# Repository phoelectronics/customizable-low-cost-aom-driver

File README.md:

# customizable-low-cost-aom-driver
Designed by Parker Osborne, University of San Diego
A custom low-cost four-channel RF signal generator that costs about $250 per board. Built around an Analog Devices AD9959 direct digital synthesizer, clocked and controlled by a raspberry Pi Pico 2W (RP2350). Features per channel: 9th order Nyquist image suppression filter, resistive pads for match and flatness, monolithic amplifier stage, +10 dBm delivered at SMA output. Tuned for 50-150 MHz output band.

The low-cost gen is built on a 4-layer RF PCB, fabricated by OSHPark. Note: When the PCB was order for the current version, a supply shortage led to a non-standard insulating core being used in this design, compared to the usual service. A stencil used for soldering the AD9959 and surround decoupling capacitors was ordered from OSH Stencils. Everything was assembled by hand using a soldering iron, hotplate, and digital microscope.

Current Version and Notes:
The low-cost generator is currently in its first working version. A second version is currently planned, with noted changes below. This design is open source and intended to be used for atomic, molecular, and optics physics, but can be implemented in a wide variety of fields. We are currently using it for doppler cooling Rb-87 atoms to create Bose-Einstein condensates. 

Current software control is limited to basic testing functions, routines can be written and triggered using spare Pico GPIO pins but are not provided here.

A full proceedings paper write up is currently planned and will be added here when completed. Currently in the final testing phase of the first design.

Note: A power supply failure burnt out the synthesizer while testing in the current version. It is suggested to remove the Vsys Pin (39) from the Raspberry Pi Pico if communication over USB serial is to be used. 

Changes for Version 2:
- adding power supply protection
- adding current limiting resistor of chip select line 
- shrinking package size of capacitors in filter

  Please reach out to me if you have any questions.

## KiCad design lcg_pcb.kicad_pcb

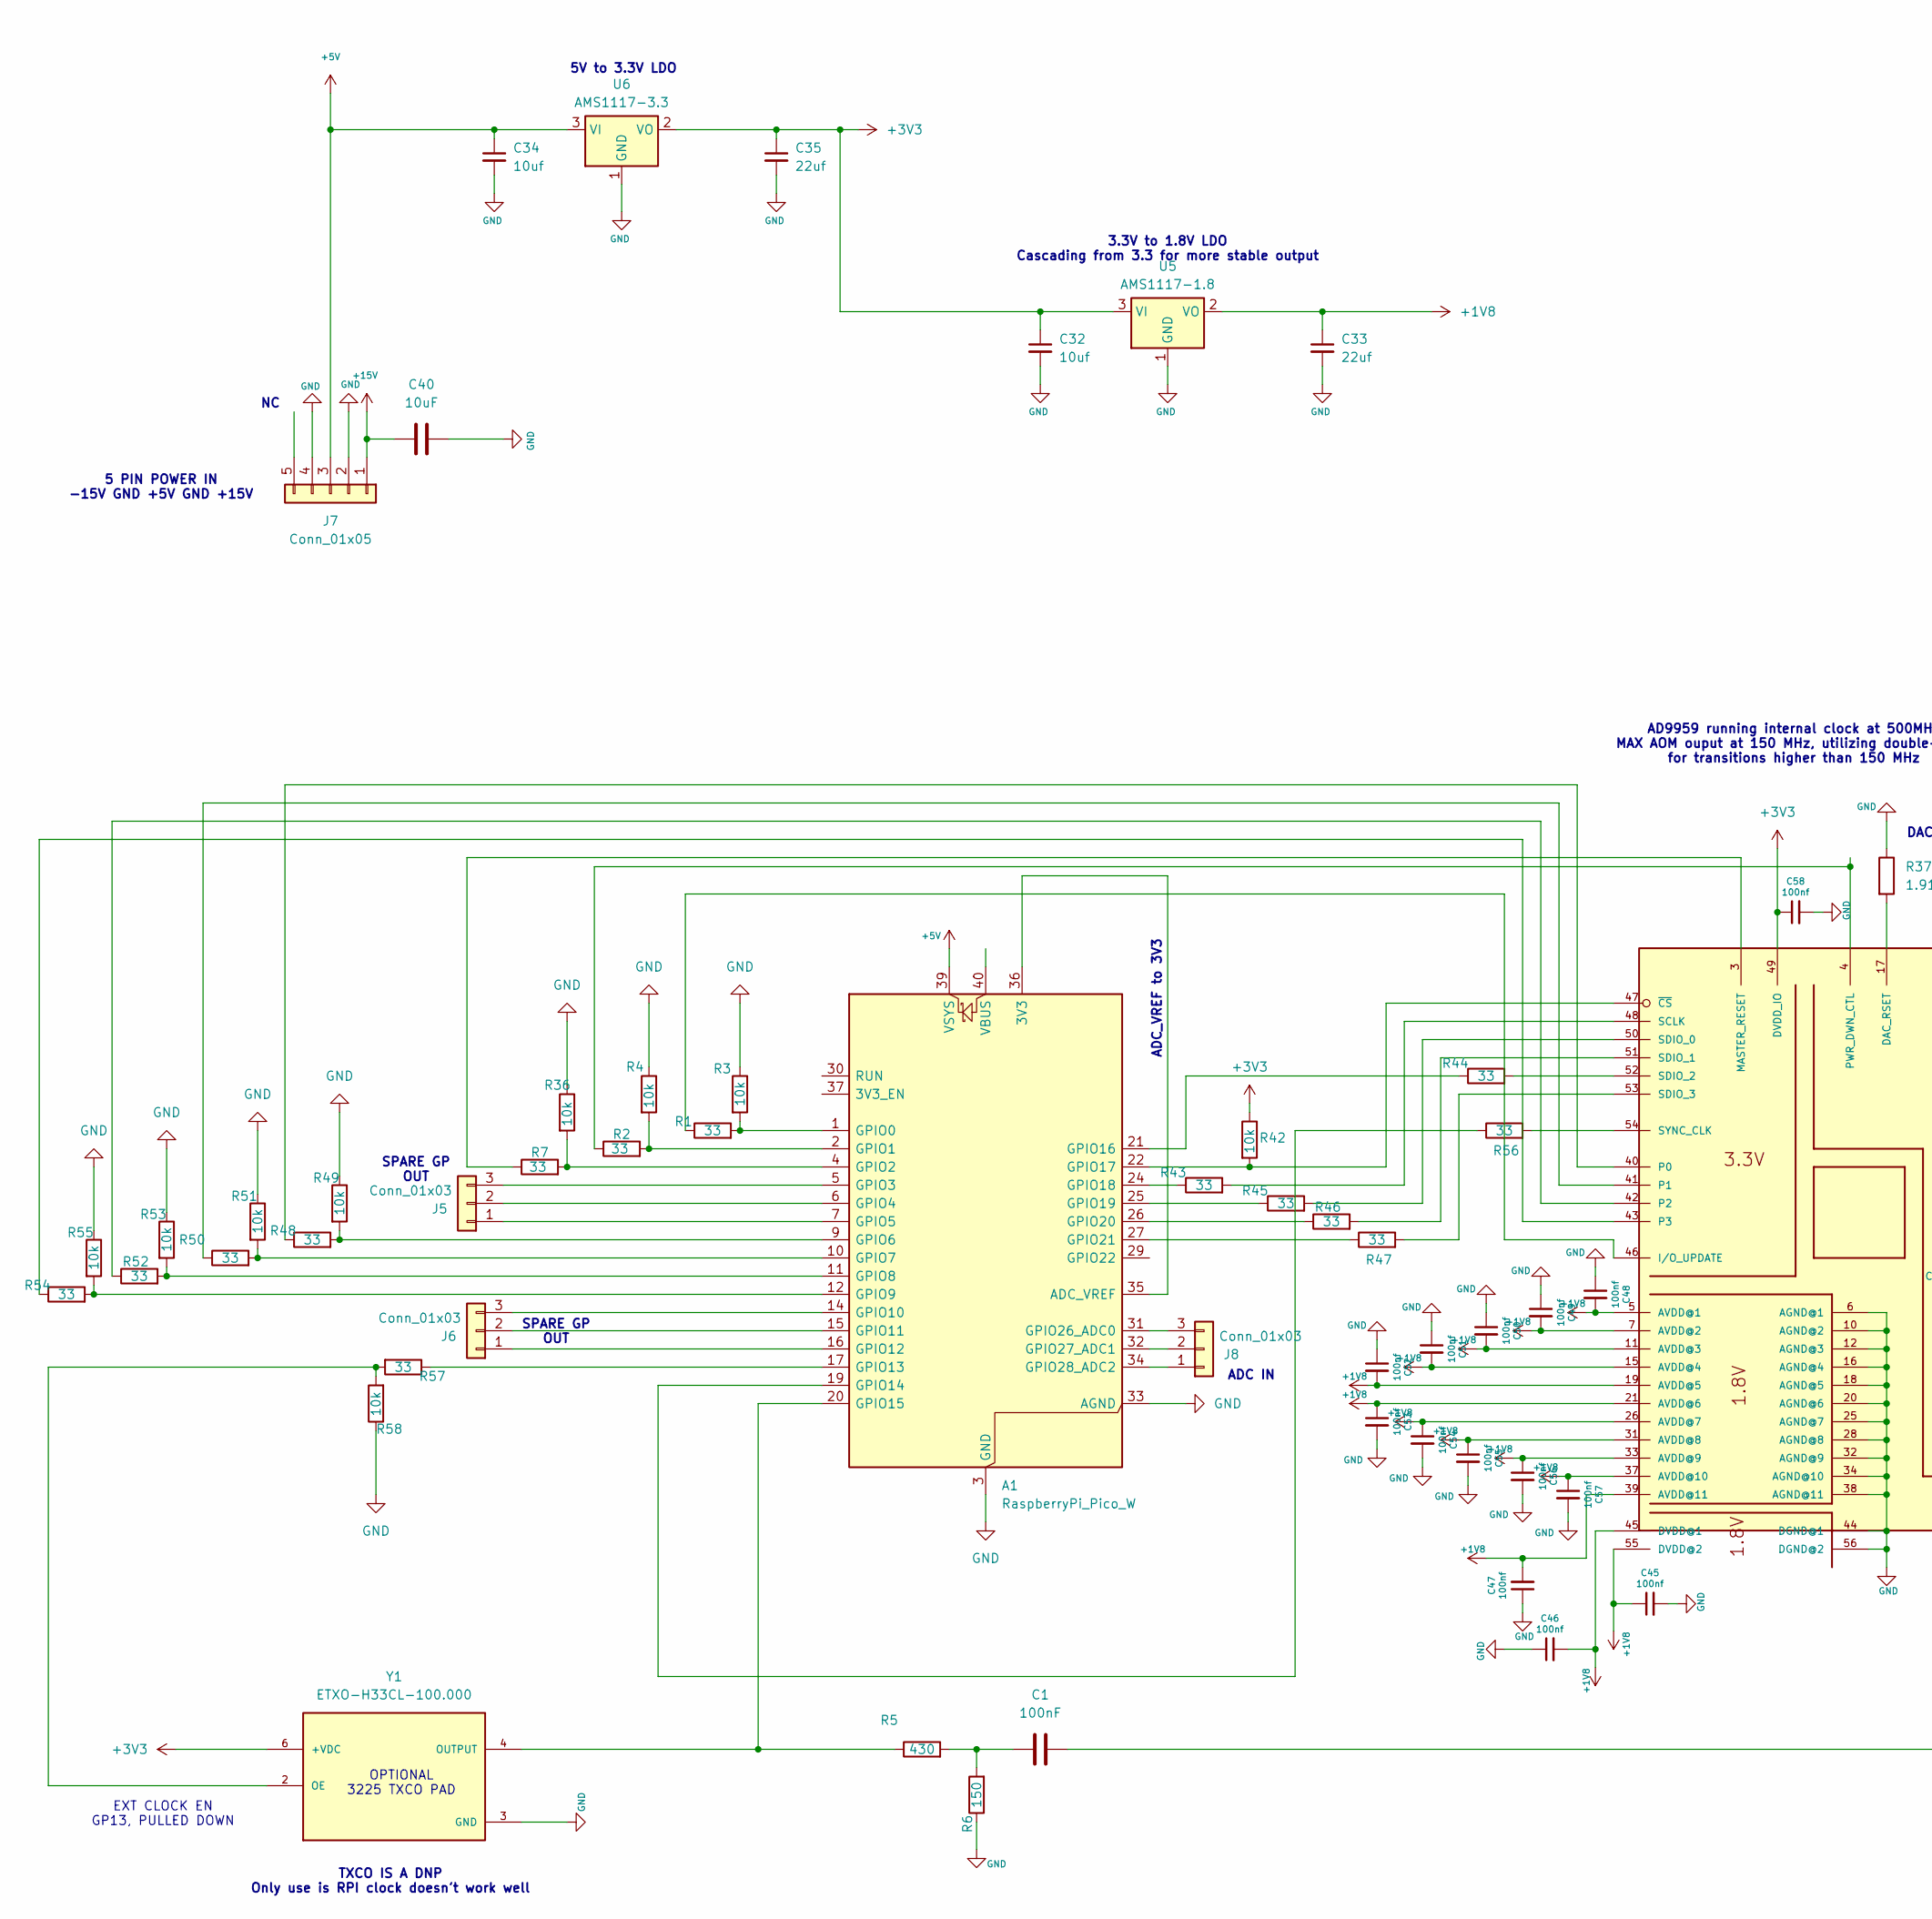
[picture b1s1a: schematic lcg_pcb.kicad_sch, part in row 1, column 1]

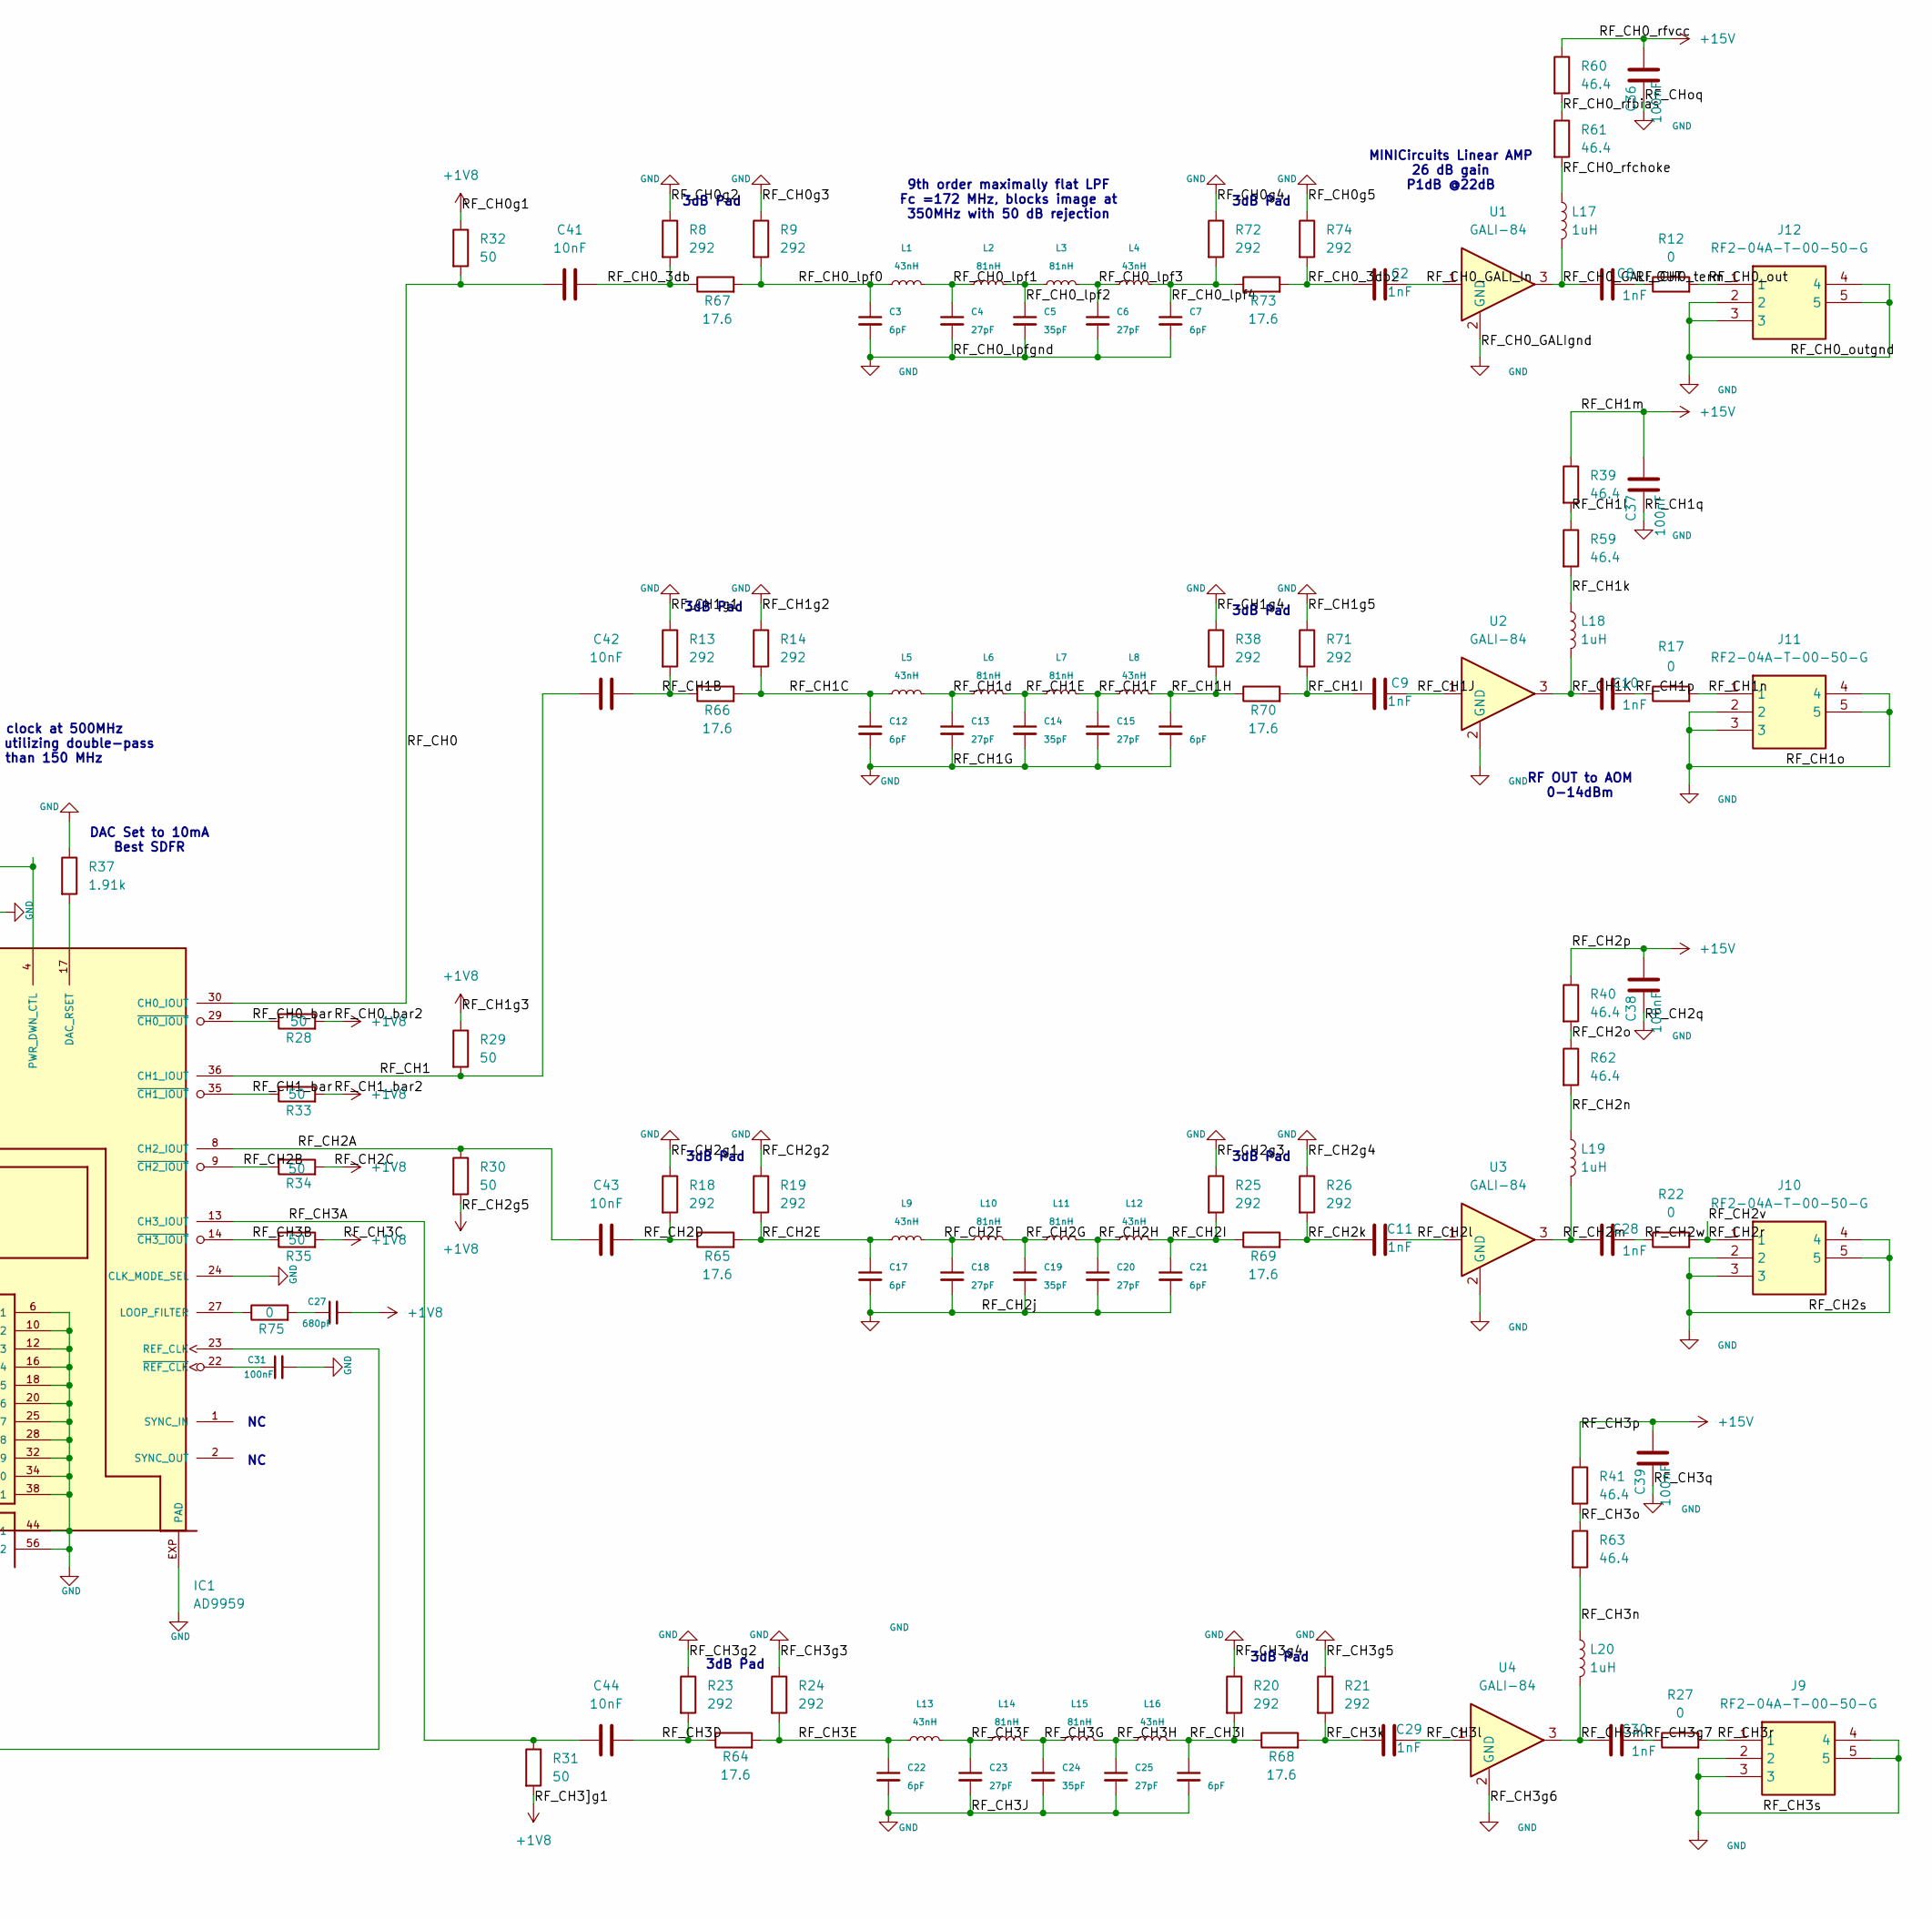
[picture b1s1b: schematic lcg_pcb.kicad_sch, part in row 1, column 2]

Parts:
A1: RaspberryPi_Pico_W; RaspberryPi_Pico_Common_THT
C1, C31, C36, C37, C38, C39: 100nF; C_1206_3216Metric_Pad1.33x1.80mm_HandSolder
C2, C8, C9, C10, C11, C28, C29, C30: 1nF; C_1206_3216Metric_Pad1.33x1.80mm_HandSolder
C3, C7, C12, C16, C17, C21, C22, C26: 6pF; C_1206_3216Metric_Pad1.33x1.80mm_HandSolder
C4, C6, C13, C15, C18, C20, C23, C25: 27pF; C_1206_3216Metric_Pad1.33x1.80mm_HandSolder
C5, C14, C19, C24: 35pF; C_1206_3216Metric_Pad1.33x1.80mm_HandSolder
C27: 680pF; C_1206_3216Metric_Pad1.33x1.80mm_HandSolder
C32, C34: 10uf; C_1206_3216Metric_Pad1.33x1.80mm_HandSolder
C33, C35: 22uf; C_1206_3216Metric_Pad1.33x1.80mm_HandSolder
C40: 10uF; C_1206_3216Metric_Pad1.33x1.80mm_HandSolder
C41, C42, C43, C44: 10nF; C_1206_3216Metric_Pad1.33x1.80mm_HandSolder
C45, C46, C47, C48, C49, C50, C51, C52, C53, C54, C55, C56, C57, C58: 100nf; C_0402_1005Metric_Pad0.74x0.62mm_HandSolder
IC1: AD9959; LFCSP56
J5, J6, J8: Conn_01x03; Molex_KK-254_AE-6410-03A_1x03_P2.54mm_Vertical
J7: Conn_01x05; Molex_KK-254_AE-6410-05A_1x05_P2.54mm_Vertical
J9, J10, J11, J12: RF2-04A-T-00-50-G; RF204AT0050G; Mouser Part Number 737-RF204AT0050G
L1, L4, L5, L8, L9, L12, L13, L16: 43nH; L_1008_2520Metric_Pad1.43x2.20mm_HandSolder
L2, L3, L6, L7, L10, L11, L14, L15: 81nH; L_1008_2520Metric_Pad1.43x2.20mm_HandSolder
L17, L18, L19, L20: 1uH; L_1206_3216Metric_Pad1.22x1.90mm_HandSolder
R1, R2, R7, R43, R44, R45, R46, R47, R48, R50, R52, R54, R56, R57: 33; R_1206_3216Metric_Pad1.30x1.75mm_HandSolder
R3, R4, R36, R42, R49, R51, R53, R55, R58: 10k; R_1206_3216Metric_Pad1.30x1.75mm_HandSolder
R5: 430; R_1206_3216Metric_Pad1.30x1.75mm_HandSolder
R6: 150; R_1206_3216Metric_Pad1.30x1.75mm_HandSolder
R8, R9, R13, R14, R18, R19, R20, R21, R23, R24, R25, R26, R38, R71, R72, R74: 292; R_1206_3216Metric_Pad1.30x1.75mm_HandSolder
R12, R17, R22, R27: 0; R_2512_6332Metric_Pad1.40x3.35mm_HandSolder
R28, R29, R30, R31, R32, R33, R34, R35: 50; R_1206_3216Metric_Pad1.30x1.75mm_HandSolder
R37: 1.91k; R_1206_3216Metric_Pad1.30x1.75mm_HandSolder
R39, R40, R41, R59, R60, R61, R62, R63: 46.4; R_2512_6332Metric_Pad1.40x3.35mm_HandSolder
R64, R65, R66, R67, R68, R69, R70, R73: 17.6; R_1206_3216Metric_Pad1.30x1.75mm_HandSolder
R75: 0; R_1206_3216Metric_Pad1.30x1.75mm_HandSolder
U1, U2, U3, U4: GALI-84; SOT-89-3
U5: AMS1117-1.8; SOT-223-3_TabPin2
U6: AMS1117-3.3; SOT-223-3_TabPin2
Y1: ETXO-H33CL-100.000; OSC_ETXO-H33CL-100.000

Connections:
+1V8: C27.2, C33.1, C45.1, C46.2, C47.2, C48.2, C49.2, C50.2, C51.2, C52.2, C53.1, C54.1, C55.1, C56.1, C57.1, IC1.5 (AVDD@1), IC1.7 (AVDD@2), IC1.11 (AVDD@3), IC1.15 (AVDD@4), IC1.19 (AVDD@5), IC1.21 (AVDD@6), IC1.26 (AVDD@7), IC1.31 (AVDD@8), IC1.33 (AVDD@9), IC1.37 (AVDD@10), IC1.39 (AVDD@11), IC1.45 (DVDD@1), IC1.55 (DVDD@2), R28.2, R29.1, R30.2, R31.2, R32.1, R33.2, R34.2, R35.2, U5.2 (VO)
+3V3: C32.1, C35.1, C58.1, IC1.49 (DVDD_IO), R42.1, U5.3 (VI), U6.2 (VO), Y1.6 (+VDC)
+5V: A1.39 (VSYS), C34.1, J7.3, U6.3 (VI)
+15V: C36.2, C37.2, C38.2, C39.2, C40.2, J7.1, R39.1, R40.1, R41.1, R60.1; also elsewhere on the board
/RF_CH0: C41.1, IC1.30 (CH0_IOUT), R32.2
/RF_CH0_3db: C41.2, R8.2, R67.1; also elsewhere on the board
/RF_CH0_3db2: C2.1, R73.2, R74.2
/RF_CH0_GALI_In: C2.2, U1.1
/RF_CH0_GALI_OUT: C8.1, L17.2, U1.3
/RF_CH0_bar: IC1.29 (~CH0_IOUT), R28.1
/RF_CH0_lpf0: C3.1, L1.1, R9.2, R67.2
/RF_CH0_lpf1: C4.1, L1.2, L2.1
/RF_CH0_lpf2: C5.1, L2.2, L3.1
/RF_CH0_lpf3: C6.1, L3.2, L4.1
/RF_CH0_lpf4: C7.1, L4.2, R72.2, R73.1
/RF_CH0_out: J12.1, R12.2
/RF_CH0_rfbias: R60.2, R61.1
/RF_CH0_rfchoke: L17.1, R61.2
/RF_CH0_term: C8.2, R12.1
/RF_CH1: C42.1, IC1.36 (CH1_IOUT), R29.2
/RF_CH1B: C42.2, R13.2, R66.1
/RF_CH1C: C12.1, L5.1, R14.2, R66.2
/RF_CH1E: C14.1, L6.2, L7.1
/RF_CH1F: C15.1, L7.2, L8.1
/RF_CH1H: C16.1, L8.2, R38.2, R70.1
/RF_CH1I: C9.1, R70.2, R71.2
/RF_CH1J: C9.2, U2.1
/RF_CH1K: C10.1, L18.2, U2.3
/RF_CH1_bar: IC1.35 (~CH1_IOUT), R33.1
/RF_CH1d: C13.1, L5.2, L6.1
/RF_CH1k: L18.1, R59.2
/RF_CH1l: R39.2, R59.1
/RF_CH1n: J11.1, R17.2
/RF_CH1p: C10.2, R17.1
/RF_CH2A: C43.1, IC1.8 (CH2_IOUT), R30.1
/RF_CH2B: IC1.9 (~CH2_IOUT), R34.1
/RF_CH2D: C43.2, R18.2, R65.1
/RF_CH2E: C17.1, L9.1, R19.2, R65.2
/RF_CH2F: C18.1, L9.2, L10.1
/RF_CH2G: C19.1, L10.2, L11.1
/RF_CH2H: C20.1, L11.2, L12.1
/RF_CH2I: C21.1, L12.2, R25.2, R69.1
/RF_CH2k: C11.1, R26.2, R69.2
/RF_CH2l: C11.2, U3.1
/RF_CH2m: C28.1, L19.2, U3.3
/RF_CH2n: L19.1, R62.2
/RF_CH2o: R40.2, R62.1
/RF_CH2r: J10.1, R22.2
/RF_CH2w: C28.2, R22.1
/RF_CH3A: C44.1, IC1.13 (CH3_IOUT), R31.1
/RF_CH3B: IC1.14 (~CH3_IOUT), R35.1
/RF_CH3D: C44.2, R23.2, R64.1
/RF_CH3E: C22.1, L13.1, R24.2, R64.2
/RF_CH3F: C23.1, L13.2, L14.1
/RF_CH3G: C24.1, L14.2, L15.1
/RF_CH3H: C25.1, L15.2, L16.1
/RF_CH3I: C26.1, L16.2, R20.2, R68.1
/RF_CH3g7: C30.2, R27.1
/RF_CH3k: C29.1, R21.2, R68.2
/RF_CH3l: C29.2, U4.1
/RF_CH3m: C30.1, L20.2, U4.3
/RF_CH3n: L20.1, R63.2
/RF_CH3o: R41.2, R63.1
/RF_CH3r: J9.1, R27.2
GND: A1.3 (GND), A1.8 (GND), A1.13 (GND), A1.18 (GND), A1.23 (GND), A1.28 (GND), A1.33 (AGND), A1.38 (GND), C3.2, C4.2, C5.2, C6.2, C7.2, C12.2, C13.2, C14.2, C15.2, C16.2, C17.2, C18.2, C19.2, C20.2, C21.2, C22.2, C23.2, C24.2, C25.2, C26.2, C31.2, C32.2, C33.2, C34.2, C35.2, C36.1, C37.1, C38.1, C39.1, C40.1, C45.2, C46.1, C47.1, C48.1, C49.1, C50.1, C51.1, C52.1, C53.2, C54.2, C55.2, C56.2, C57.2, C58.2, IC1.6 (AGND@1), IC1.10 (AGND@2), IC1.12 (AGND@3), IC1.16 (AGND@4), IC1.18 (AGND@5), IC1.20 (AGND@6), IC1.24 (CLK_MODE_SEL), IC1.25 (AGND@7), IC1.28 (AGND@8), IC1.32 (AGND@9), IC1.34 (AGND@10), IC1.38 (AGND@11), IC1.44 (DGND@1), IC1.56 (DGND@2), IC1.EXP (PAD), J7.2, J7.4, J9.2, J9.3, J9.4, J9.5, J10.2, J10.3, J10.4, J10.5, J11.2, J11.3, J11.4, J11.5, J12.2, J12.3, J12.4, J12.5, R3.1, R4.1, R6.1, R8.1, R9.1, R13.1, R14.1, R18.1, R19.1, R20.1, R21.1, R23.1, R24.1, R25.1, R26.1, R36.1, R37.1, R38.1, R49.1, R51.1, R53.1, R55.1, R58.1, R71.1, R72.1, R74.1, U1.2 (GND_2), U2.2 (GND_2), U3.2 (GND_2), U4.2 (GND_2), U5.1 (GND), U6.1 (GND), Y1.3 (GND); also elsewhere on the board
unnamed: A1.35 (ADC_VREF), A1.36 (3V3)
unnamed: A1.1 (GPIO0), R1.2, R3.2
unnamed: A1.2 (GPIO1), R2.2, R4.2
unnamed: A1.4 (GPIO2), R7.2, R36.2
unnamed: A1.5 (GPIO3), J5.3
unnamed: A1.6 (GPIO4), J5.2
unnamed: A1.7 (GPIO5), J5.1
unnamed: A1.9 (GPIO6), R48.2, R49.2
unnamed: A1.10 (GPIO7), R50.2, R51.2
unnamed: A1.11 (GPIO8), R52.2, R53.2
unnamed: A1.12 (GPIO9), R54.2, R55.2
unnamed: A1.14 (GPIO10), J6.3
unnamed: A1.15 (GPIO11), J6.2
unnamed: A1.16 (GPIO12), J6.1
unnamed: A1.17 (GPIO13), R57.1
unnamed: A1.19 (GPIO14), R56.1
unnamed: A1.20 (GPIO15), R5.1, Y1.4 (OUTPUT)
unnamed: A1.21 (GPIO16), R44.1
unnamed: A1.22 (GPIO17), IC1.47 (~CS), R42.2
unnamed: A1.24 (GPIO18), R43.1
unnamed: A1.25 (GPIO19), R45.1
unnamed: A1.26 (GPIO20), R46.1
unnamed: A1.27 (GPIO21), R47.1
unnamed: A1.31 (GPIO26_ADC0), J8.3
unnamed: A1.32 (GPIO27_ADC1), J8.2
unnamed: A1.34 (GPIO28_ADC2), J8.1
unnamed: C1.1, R5.2, R6.2
unnamed: C27.1, R75.2
unnamed: IC1.17 (DAC_RSET), R37.2
unnamed: IC1.46 (I/O_UPDATE), R1.1
unnamed: IC1.27 (LOOP_FILTER), R75.1
unnamed: IC1.3 (MASTER_RESET), R7.1
unnamed: IC1.40 (P0), R48.1
unnamed: IC1.41 (P1), R50.1
unnamed: IC1.42 (P2), R52.1
unnamed: IC1.43 (P3), R54.1
unnamed: IC1.4 (PWR_DWN_CTL), R2.1
unnamed 102: C1.2, IC1.23 (REF_CLK); also elsewhere on the board
unnamed: IC1.48 (SCLK), R43.2
unnamed 104: IC1.50 (SDIO_0), R45.2; also elsewhere on the board
unnamed: IC1.51 (SDIO_1), R46.2
unnamed: IC1.52 (SDIO_2), R44.2
unnamed: IC1.53 (SDIO_3), R47.2
unnamed: IC1.54 (SYNC_CLK), R56.2
unnamed: C31.1, IC1.22 (~REF_CLK)
unnamed: R57.2, R58.2, Y1.2 (OE)

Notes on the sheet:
ADC IN
DAC Set to 10mA Best SDFR
3dB Pad
ADC_VREF to 3V3
MINICircuits Linear AMP 26 dB gain P1dB @22dB
9th order maximally flat LPF Fc =172 MHz, blocks image at 350MHz with 50 dB rejection
SPARE GP OUT
3.3V to 1.8V LDO Cascading from 3.3 for more stable output
OPTIONAL 3225 TXCO PAD
AD9959 running internal clock at 500MHz MAX AOM ouput at 150 MHz, utilizing double-pass for transitions higher than 150 MHz
5 PIN POWER IN -15V GND +5V GND +15V
RF OUT to AOM 0-14dBm
EXT CLOCK EN GP13, PULLED DOWN
5V to 3.3V LDO
TXCO IS A DNP Only use is RPI clock doesn't work well

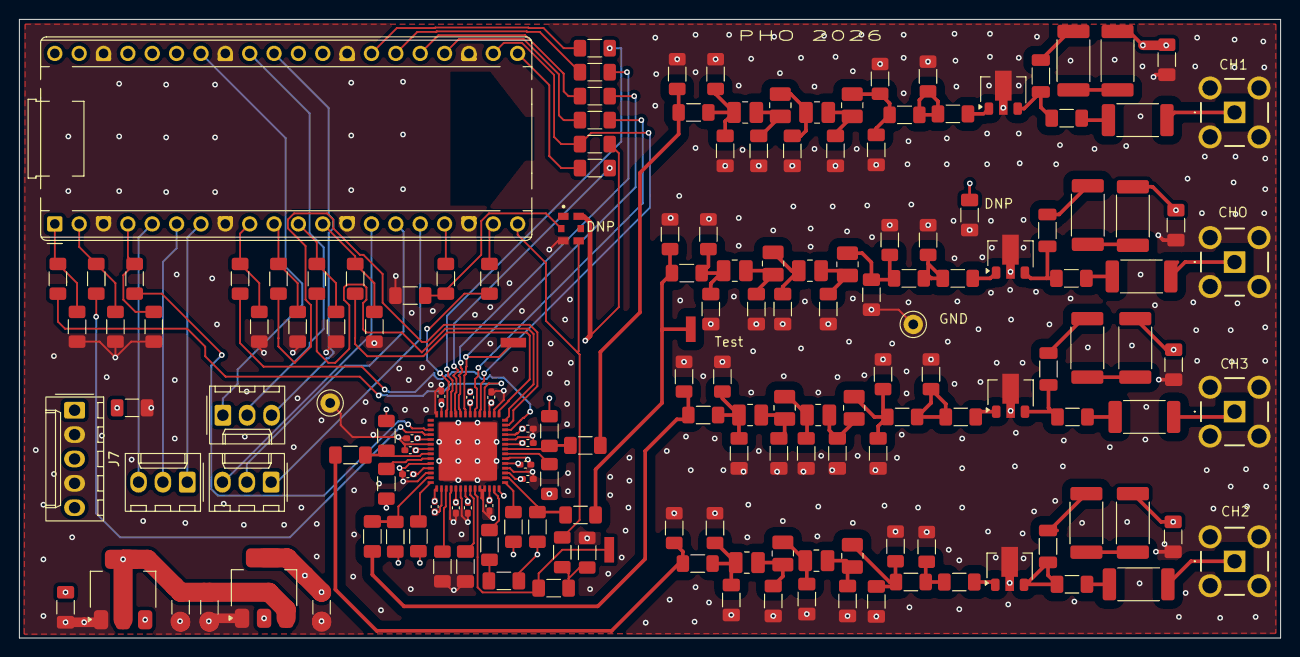
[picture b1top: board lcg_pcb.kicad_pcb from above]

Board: 4 copper layers, 131.5 x 64.5 mm, 172 parts (0 on the bottom side), 111 nets.

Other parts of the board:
C59: 10uF; C_1206_3216Metric_Pad1.33x1.80mm_HandSolder
TP2, TP4, TP5: 5015; Test_Point_2.67x1.02mm
TP6, TP7: 5001; Test_Point_D1.02mm

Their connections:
+15V: C59.2; also elsewhere on the board
/RF_CH0_3db: TP2.1 (~_1); also elsewhere on the board
GND: C59.1, TP6.1 (~_1), TP7.1 (~_1); also elsewhere on the board
unnamed 102: TP4.1 (~_1); also elsewhere on the board
unnamed 104: TP5.1 (~_1); also elsewhere on the board
